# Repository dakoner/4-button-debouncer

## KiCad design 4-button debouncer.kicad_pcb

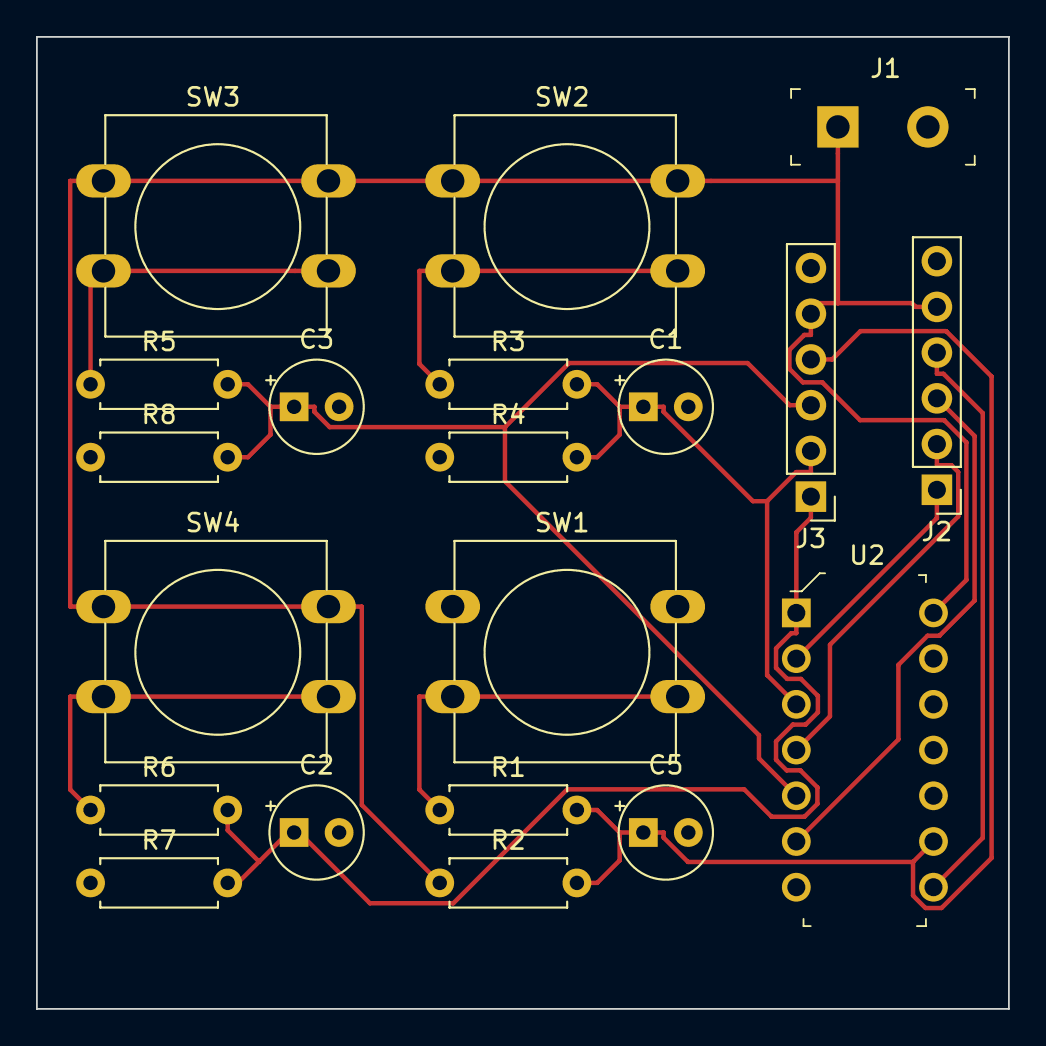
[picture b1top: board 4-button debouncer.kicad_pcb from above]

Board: 2 copper layers, 54.0 x 54.0 mm, 20 parts (0 on the bottom side), 14 nets.

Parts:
C1, C2, C3, C5: 1uF; CP_Radial_Tantal_D5.0mm_P2.50mm
J1: 1935161; Terminal_Block_D1.3mm_P5mm
J2, J3: Conn_01x06; PinHeader_1x06_P2.54mm_Vertical
R1, R3, R5, R6: 10k; R_Axial_DIN0207_L6.3mm_D2.5mm_P7.62mm_Horizontal
R2, R4, R7, R8: 100k; R_Axial_DIN0207_L6.3mm_D2.5mm_P7.62mm_Horizontal
SW1, SW2, SW3, SW4: SW_Push; SW_PUSH-12mm
U2: SN74HC14N; DIP-14_W3mm

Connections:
+5V: J1.1, J2.5, J3.5, R2.1, SW2.1, SW3.1, SW4.1, U2.14 (VCC)
/SW1: C2.1, J3.1, R6.2, R7.2, U2.1 (1A)
/SW2: C1.1, J3.2, R3.2, R4.2, U2.3 (2A)
/SW3: C3.1, J3.3, R5.2, R8.2, U2.5 (3A)
/SW4: C5.1, J3.4, R1.2, R2.2, U2.9 (4A)
GND: C1.2, C2.2, C3.2, C5.2, J1.2, J2.6, J3.6, R4.1, R7.1, R8.1, SW1.1, U2.7 (GND), U2.11 (5A), U2.13 (6A)
unnamed: J2.1, U2.2 (1Y)
unnamed: J2.2, U2.4 (2Y)
unnamed: J2.3, U2.6 (3Y)
unnamed: J2.4, U2.8 (4Y)
unnamed: R1.1, SW1.2
unnamed: R3.1, SW2.2
unnamed: R5.1, SW3.2
unnamed: R6.1, SW4.2
